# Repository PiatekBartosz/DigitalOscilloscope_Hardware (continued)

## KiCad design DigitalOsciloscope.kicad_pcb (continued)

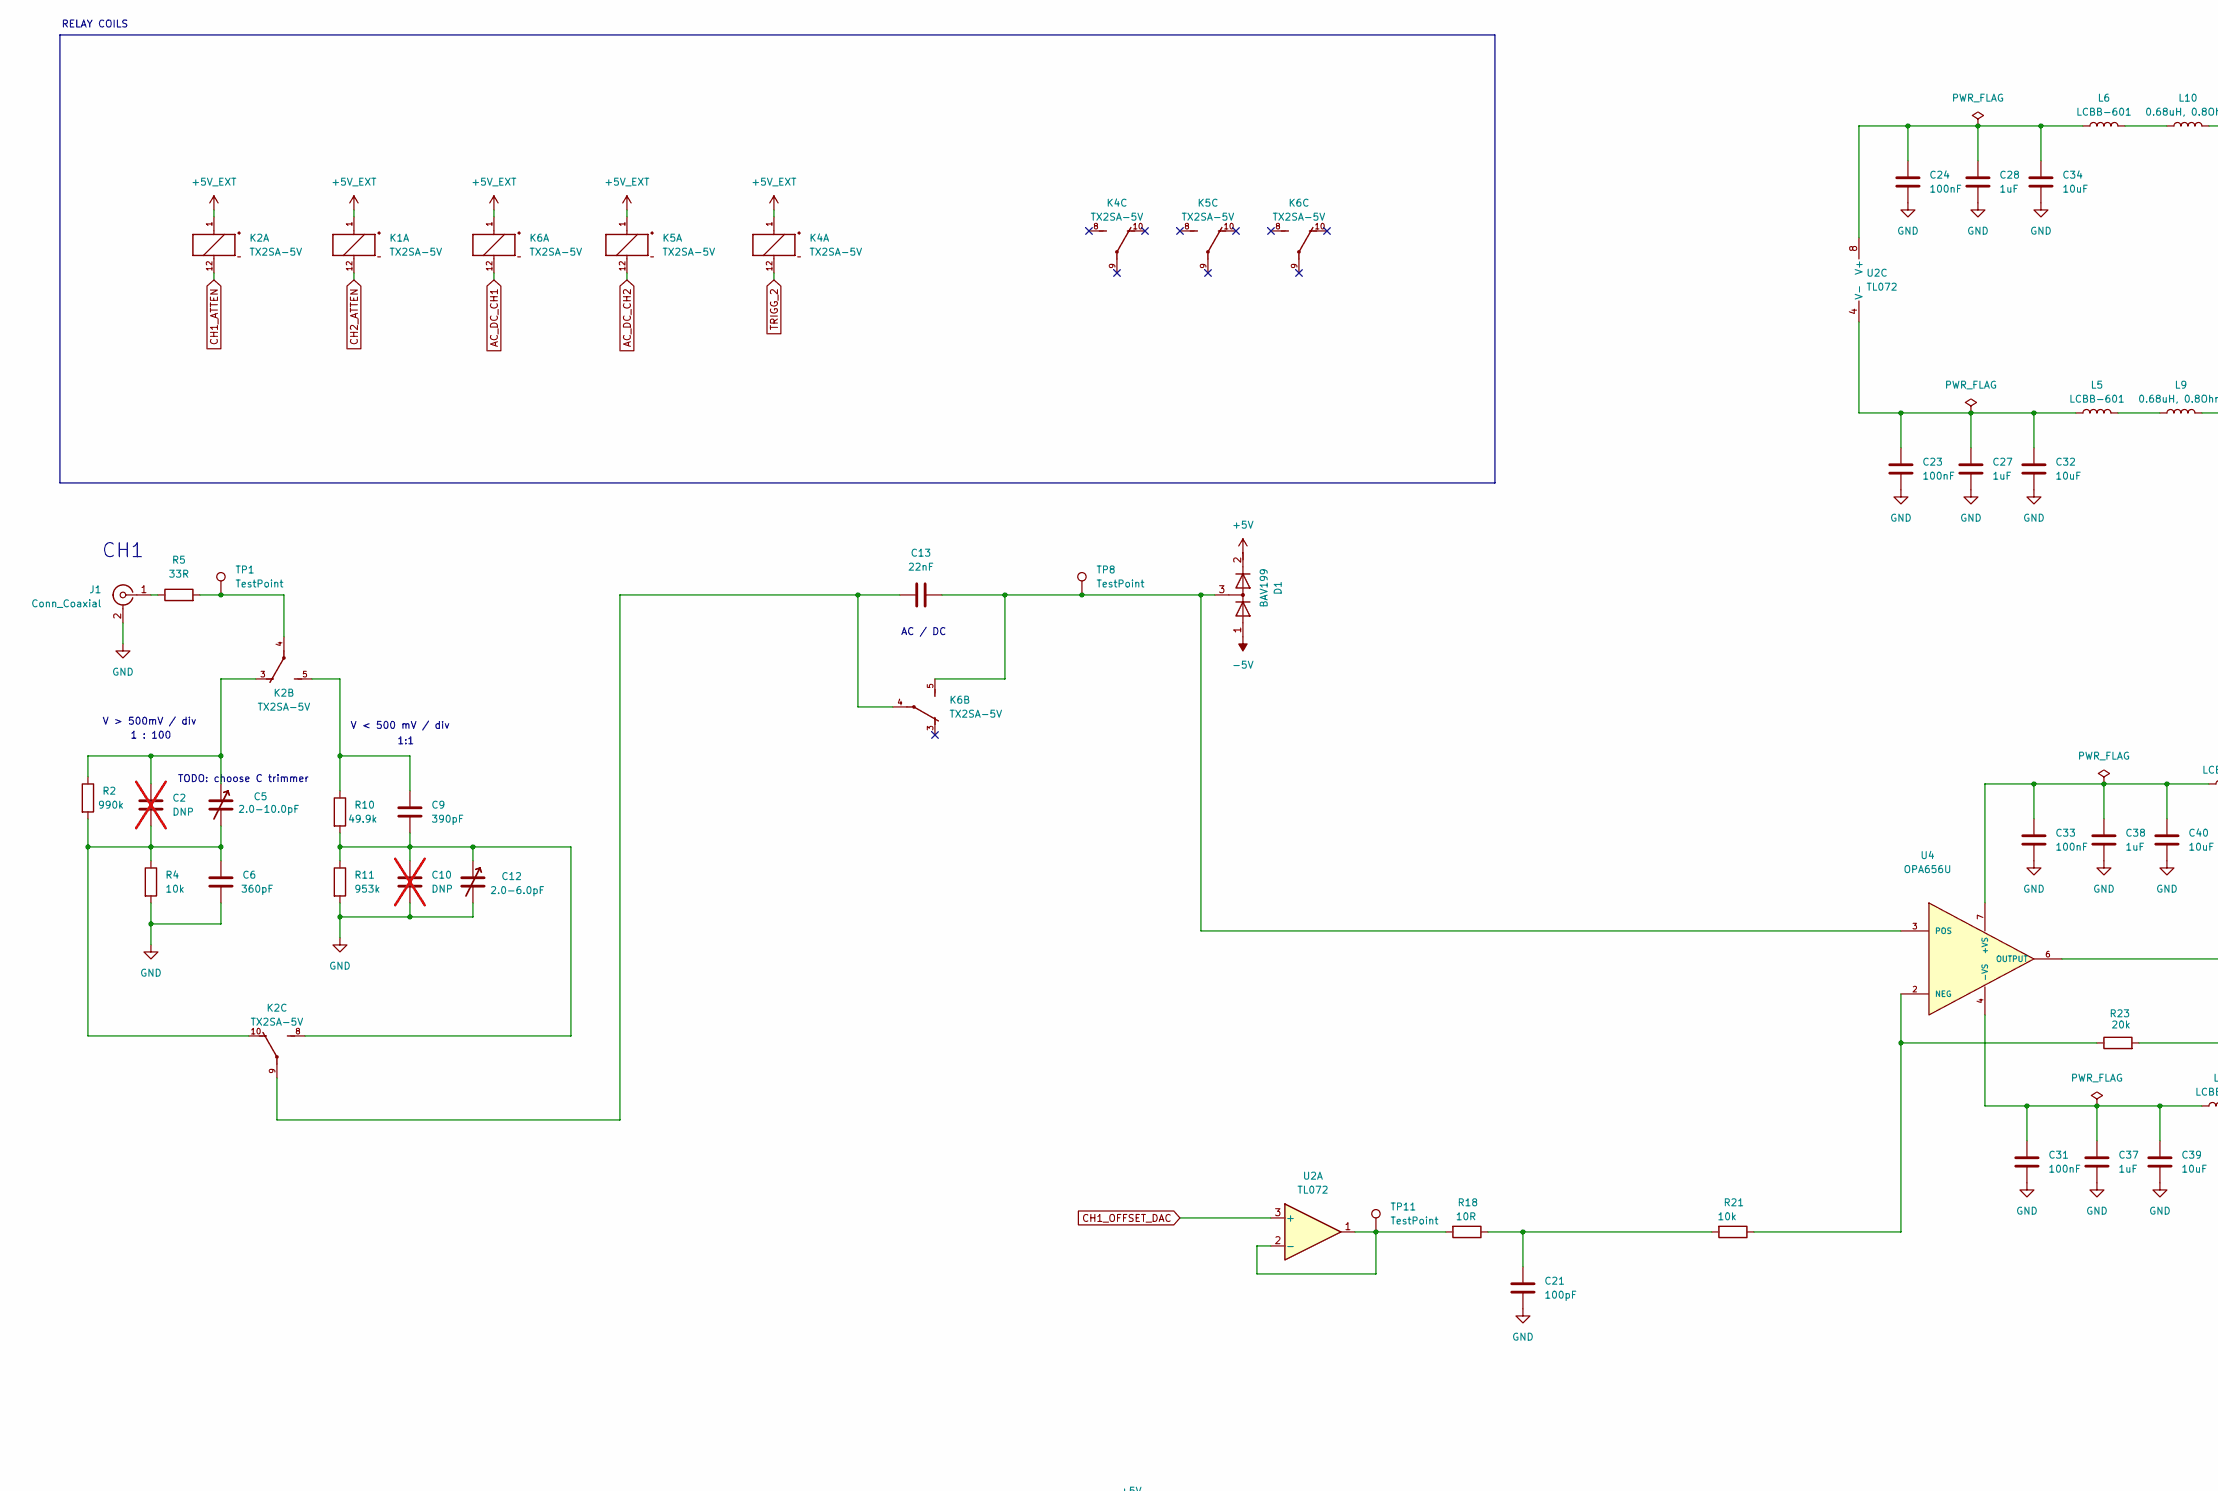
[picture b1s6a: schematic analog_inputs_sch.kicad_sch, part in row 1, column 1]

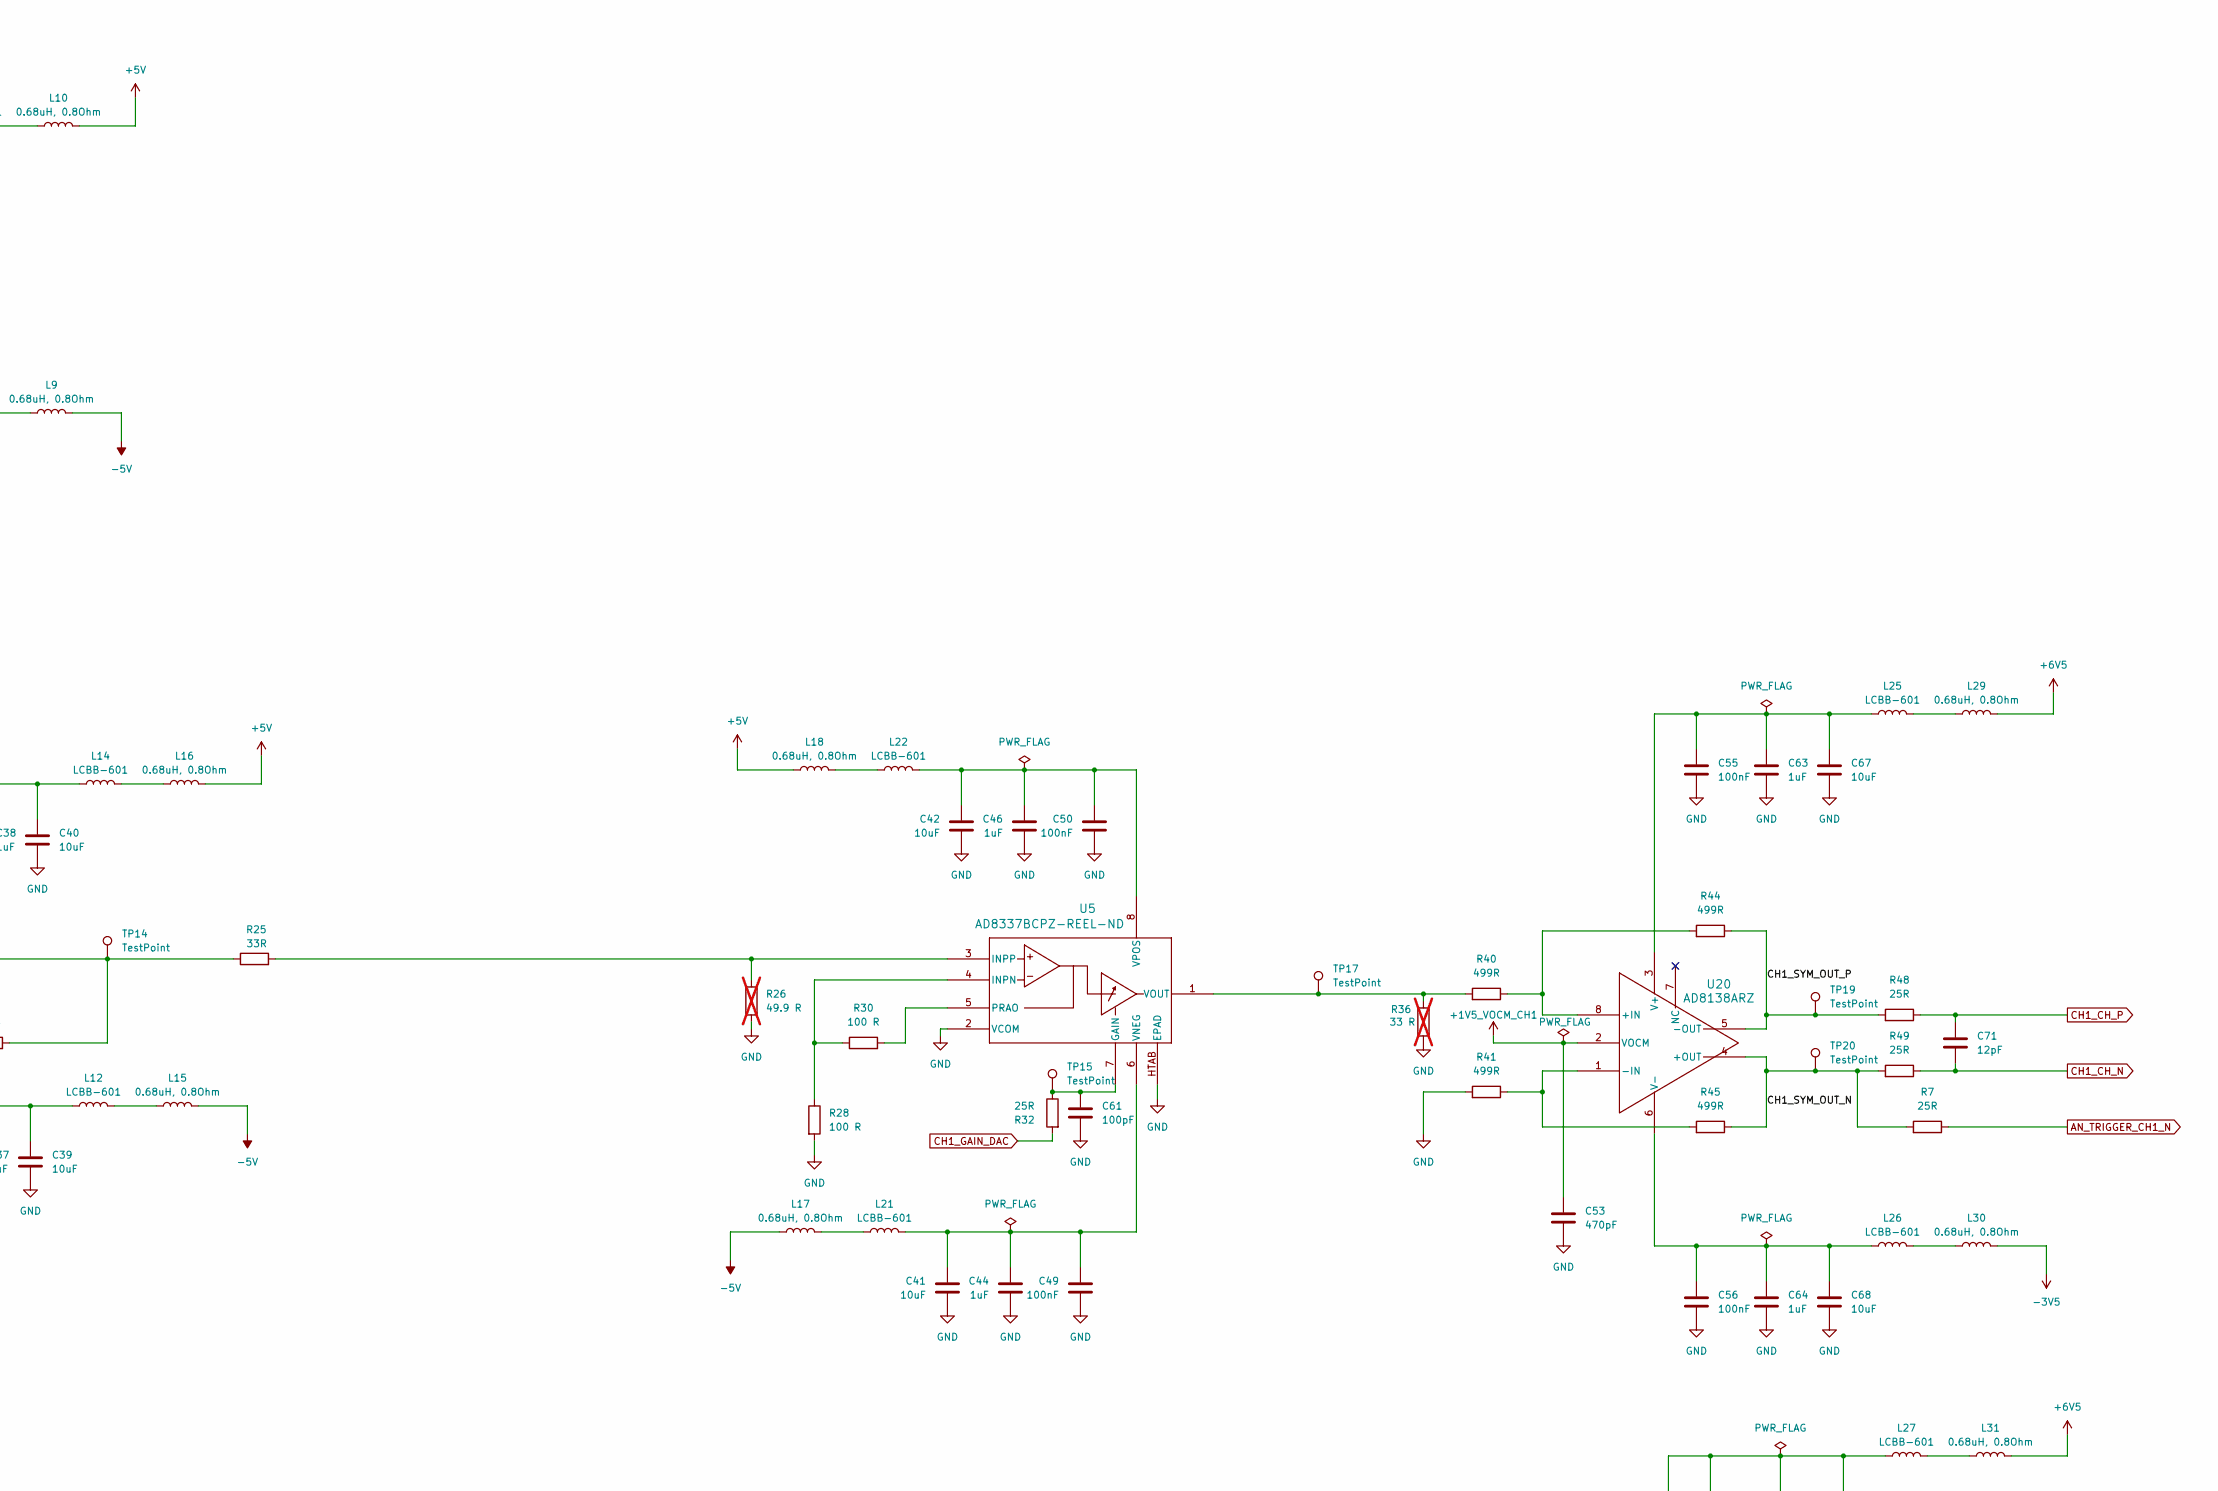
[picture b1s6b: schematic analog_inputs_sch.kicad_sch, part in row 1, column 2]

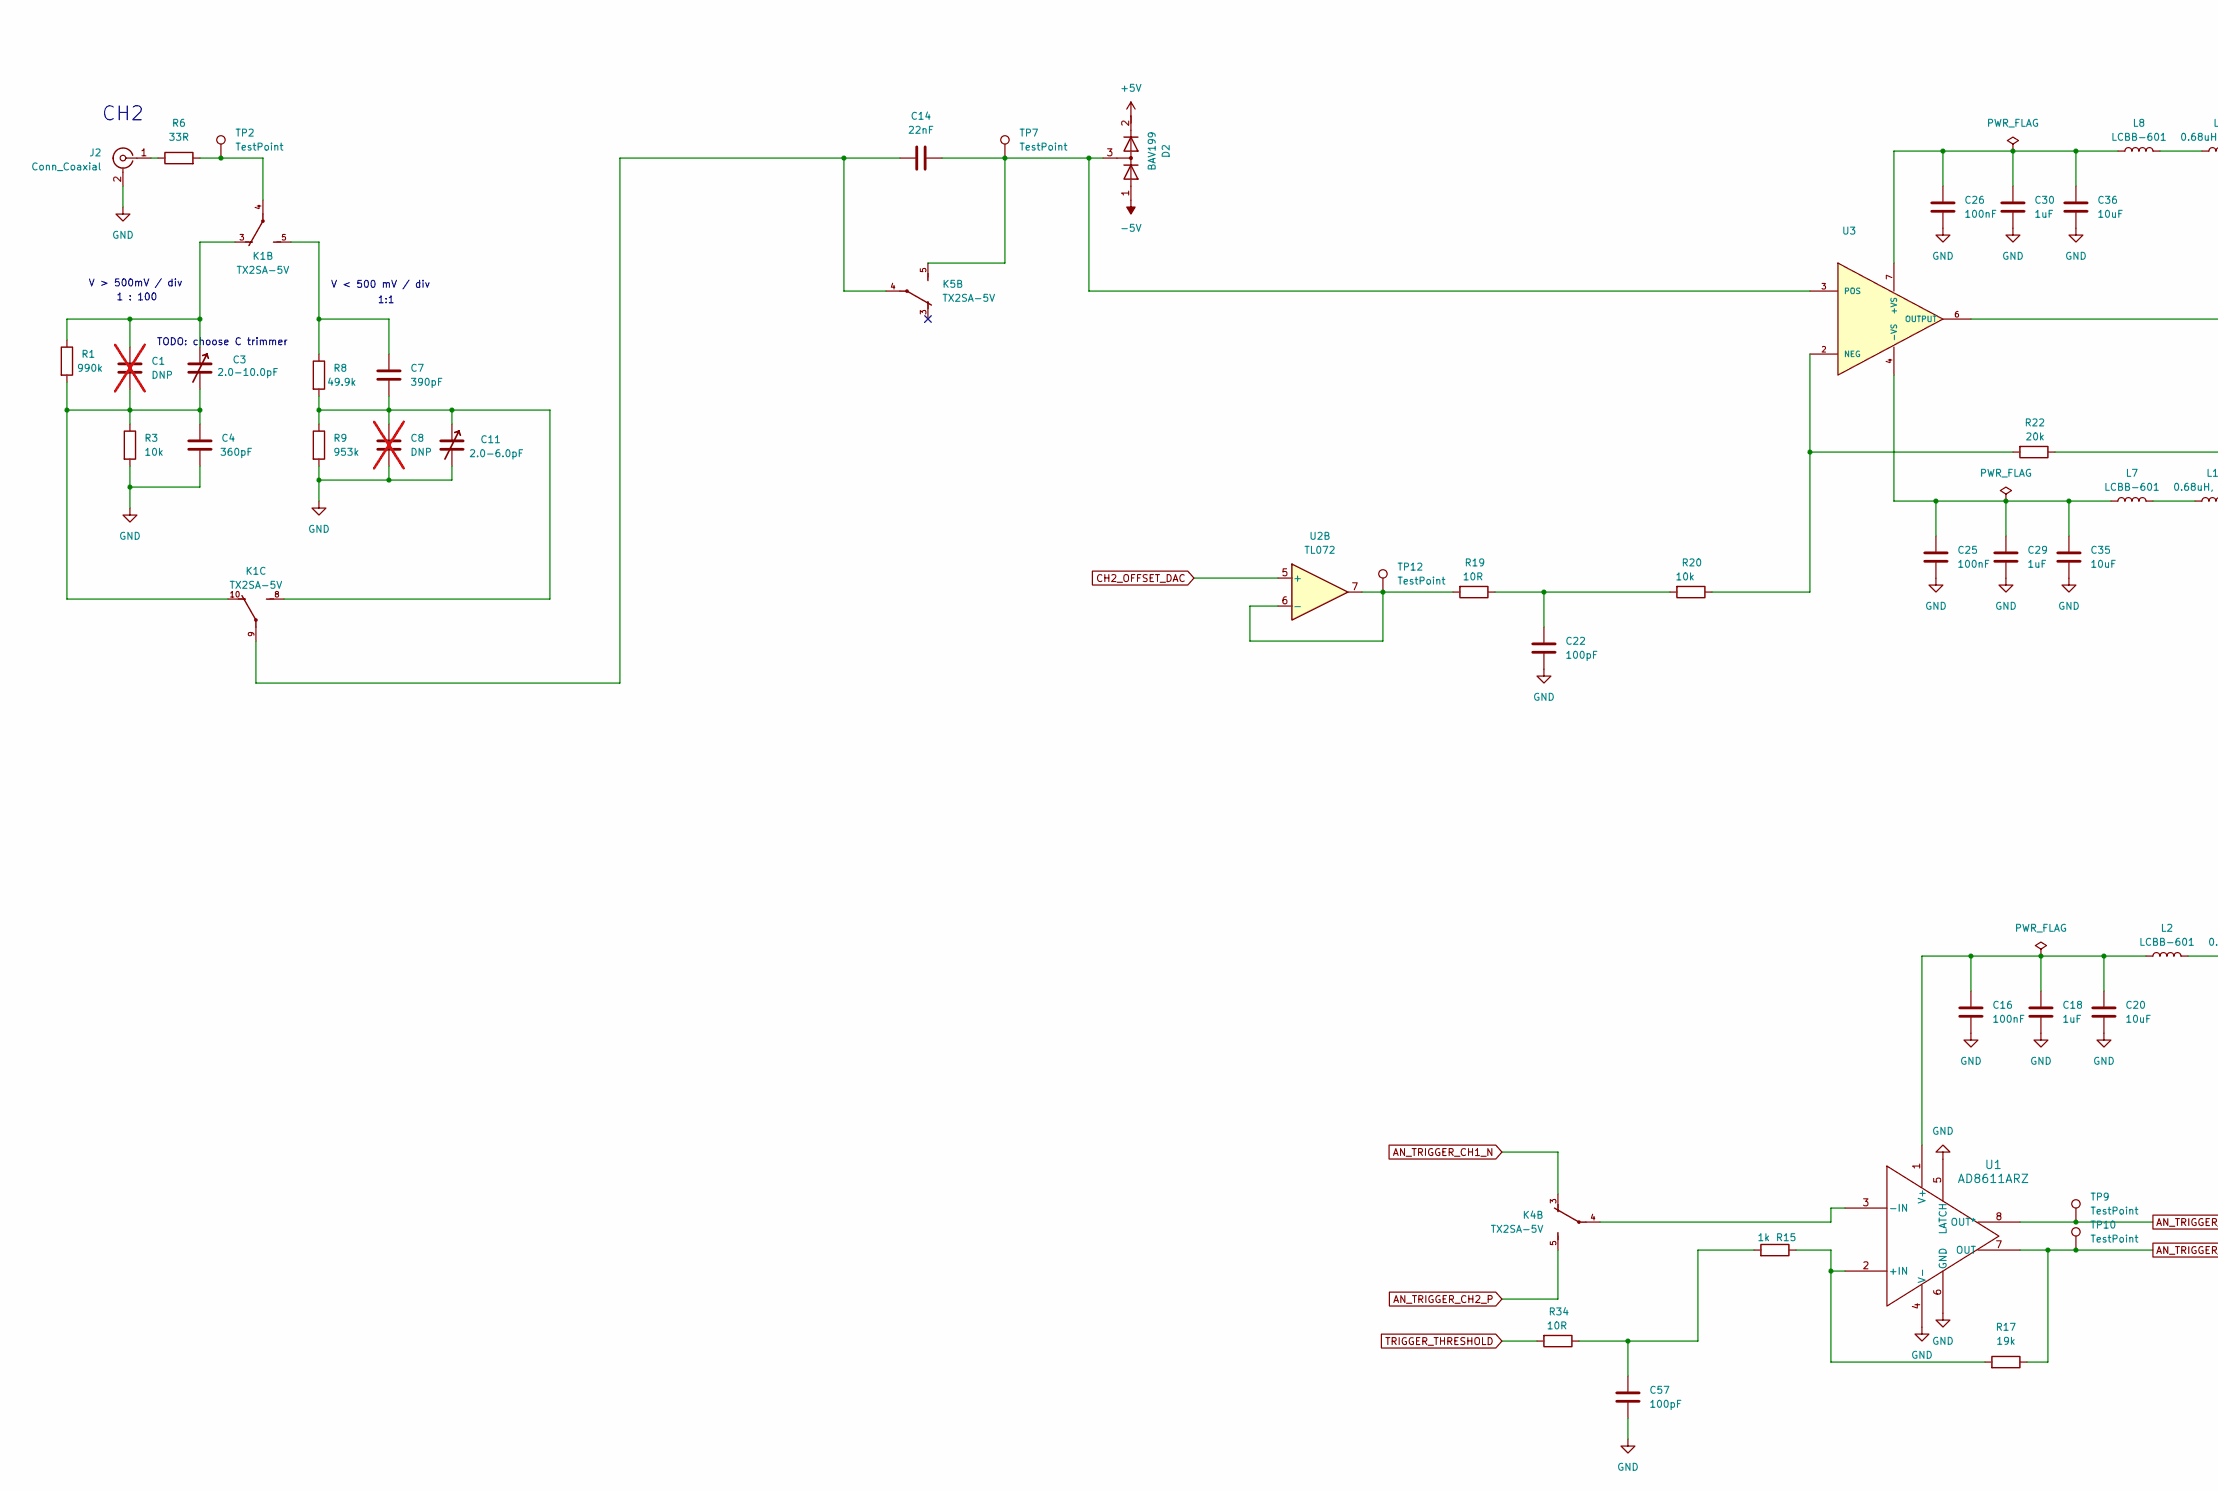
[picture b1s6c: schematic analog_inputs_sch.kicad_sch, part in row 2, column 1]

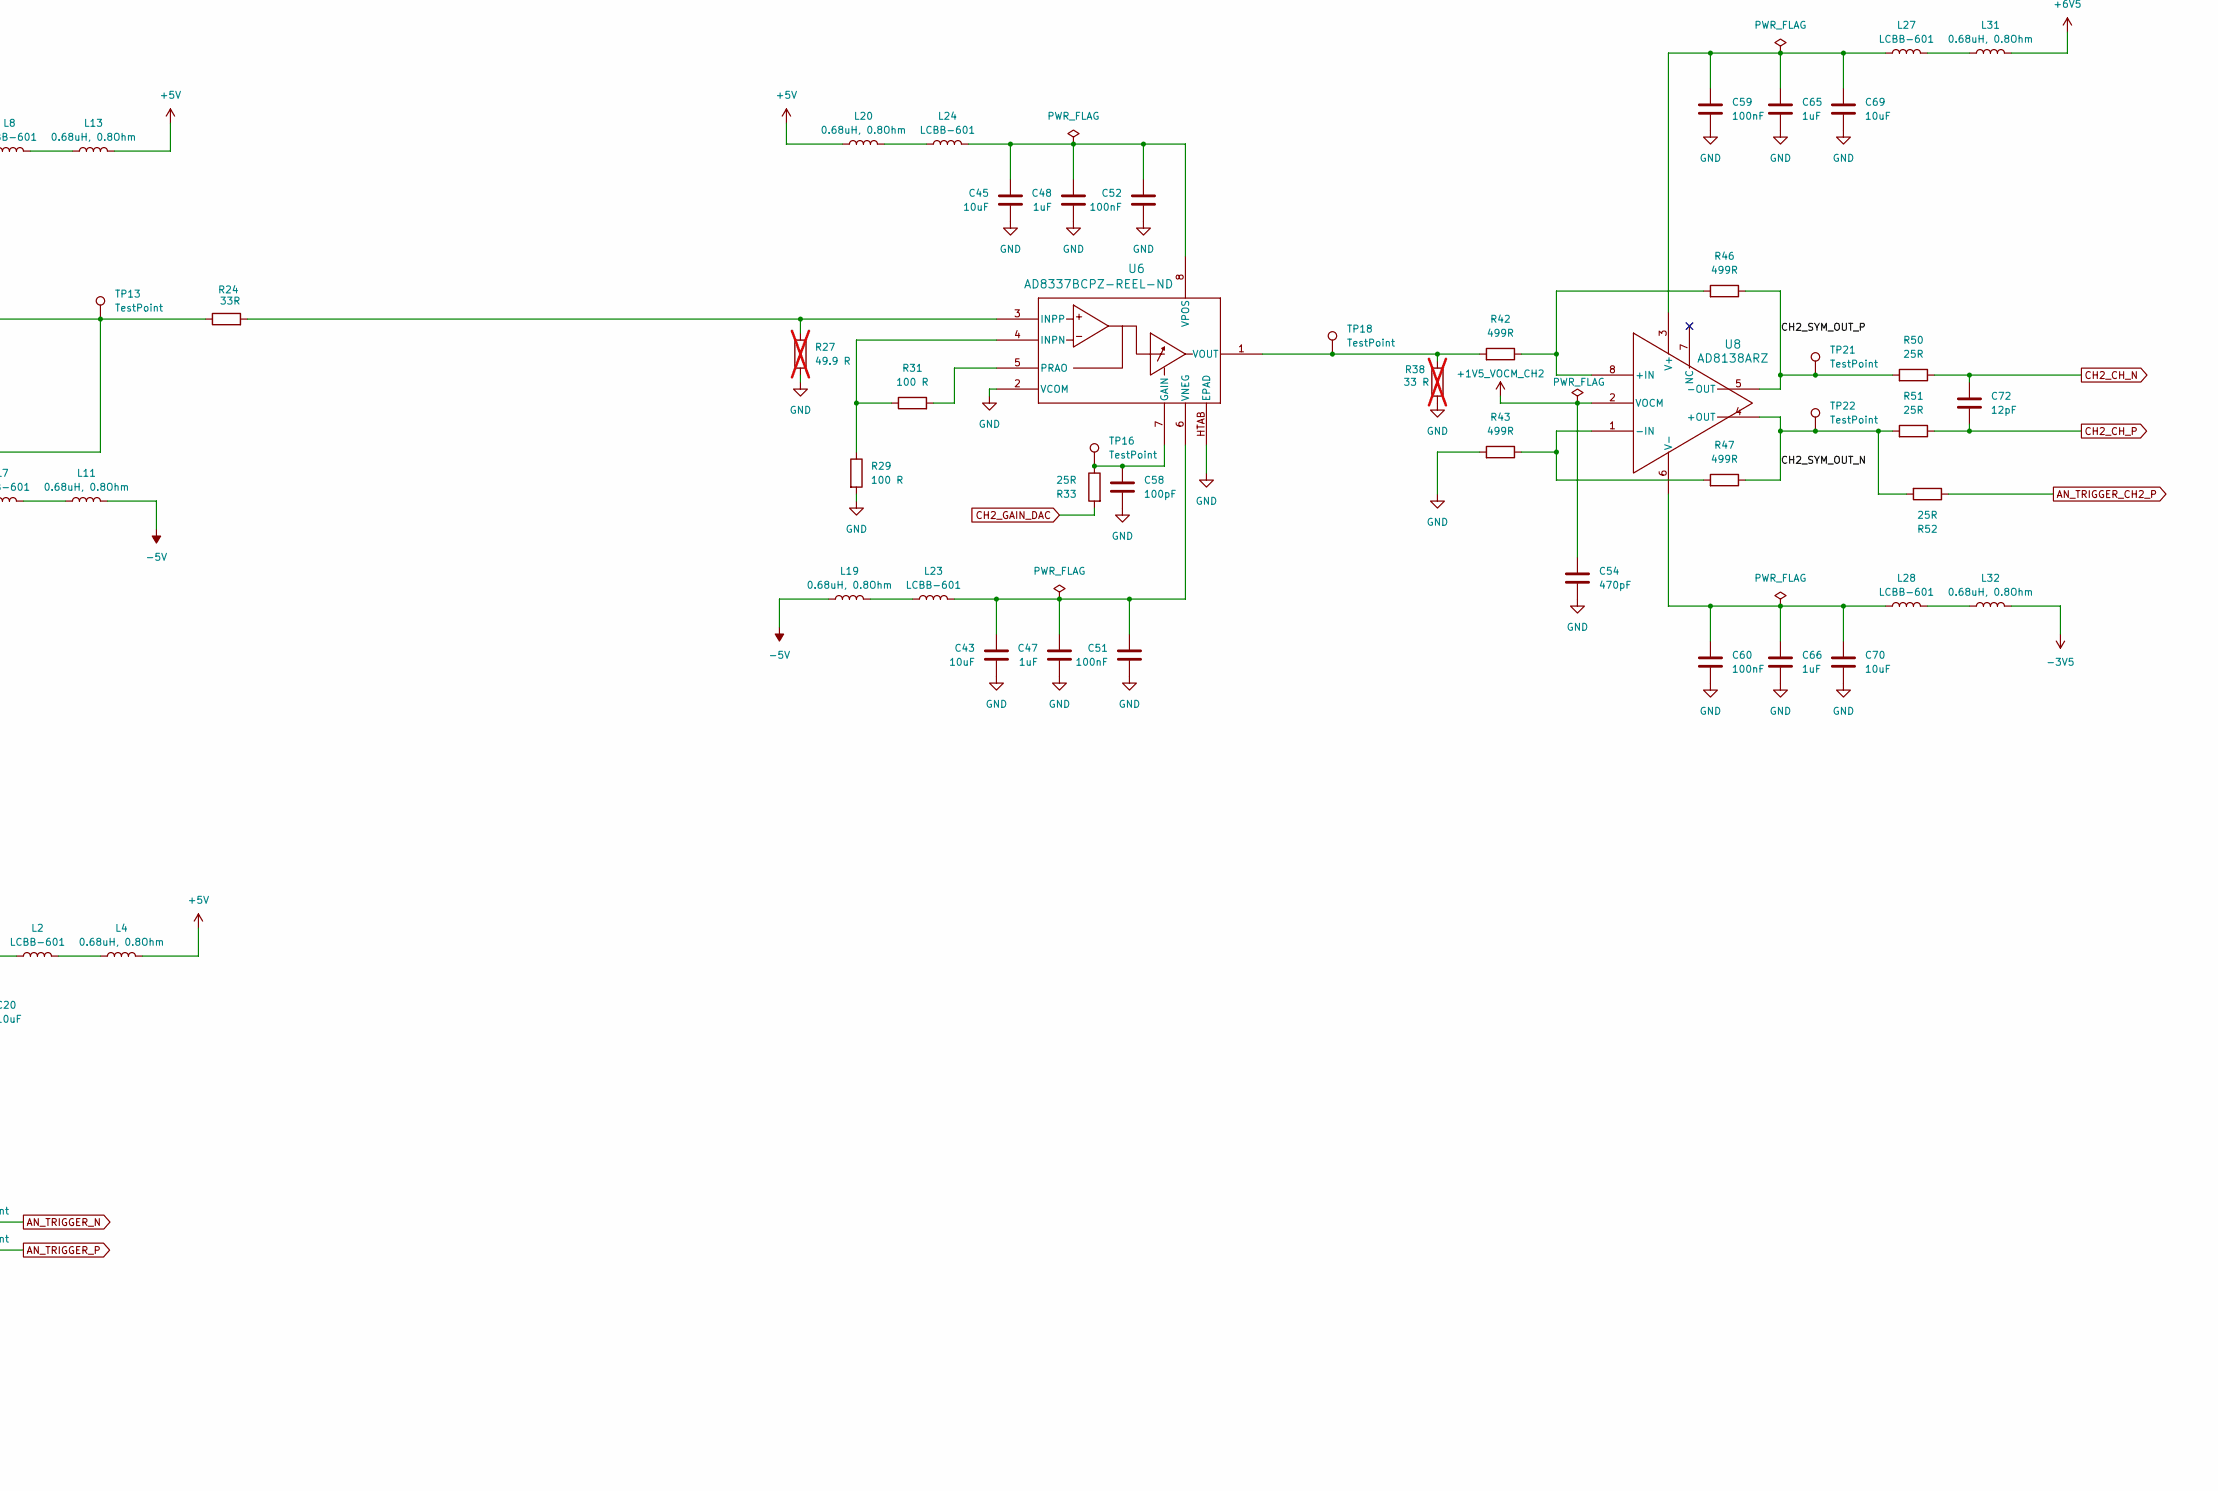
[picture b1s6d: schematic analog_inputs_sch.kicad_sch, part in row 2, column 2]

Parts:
C1, C2, C8, C10: DNP; C_0805_2012Metric; not fitted
C3, C5: 2.0-10.0pF; C_Trimmer_Voltronics_JZ
C4, C6: 360pF; C_0805_2012Metric
C7, C9: 390pF; C_0805_2012Metric
C11, C12: 2.0-6.0pF; C_Trimmer_Voltronics_JZ
C13, C14: 22nF; C_0805_2012Metric
C16, C23, C24, C25, C26, C31, C33, C49, C50, C51, C52, C55, C56, C59, C60: 100nF; C_0805_2012Metric
C18, C27, C28, C29, C30, C37, C38, C44, C46, C47, C48, C63, C64, C65, C66: 1uF; C_0805_2012Metric
C20, C32, C34, C35, C36, C39, C40, C41, C42, C43, C45, C67, C68, C69, C70: 10uF; C_0805_2012Metric
C21, C22, C57, C58, C61: 100pF; C_0805_2012Metric
C53, C54: 470pF; C_0805_2012Metric
C71, C72: 12pF; C_0805_2012Metric
D1, D2: BAV199; SOT-23
J1, J2: Conn_Coaxial; BNC_Amphenol_B6252HB-NPP3G-50_Horizontal
K1, K2, K4, K5, K6: TX2SA-5V; RELAY_TX2SA_PAN; FARNELL 1175716
L2, L5, L6, L7, L8, L12, L14, L21, L22, L23, L24, L25, L26, L27, L28: LCBB-601; L_0805_2012Metric
L4, L9, L10, L11, L13, L15, L16, L17, L18, L19, L20, L29, L30, L31, L32: 0.68uH, 0.8Ohm; L_0805_2012Metric
R1, R2: 990k; R_0805_2012Metric
R3, R4, R20, R21: 10k; R_0805_2012Metric
R5, R6, R24, R25: 33R; R_0805_2012Metric
R7, R32, R33, R48, R49, R50, R51, R52: 25R; R_0805_2012Metric
R8, R10: 49.9k; R_0805_2012Metric
R9, R11: 953k; R_0805_2012Metric
R15: 1k; R_0805_2012Metric
R17: 19k; R_0805_2012Metric
R18, R19, R34: 10R; R_0805_2012Metric
R22, R23: 20k; R_0805_2012Metric
R26, R27: 49.9 R; R_0805_2012Metric; not fitted
R28, R29, R30, R31: 100 R; R_0805_2012Metric
R36, R38: 33 R; R_0805_2012Metric; not fitted
R40, R41, R42, R43, R44, R45, R46, R47: 499R; R_0805_2012Metric
TP1, TP2, TP7, TP8, TP9, TP10, TP11, TP12, TP13, TP14, TP15, TP16, TP17, TP18, TP19, TP20, TP21, TP22: TestPoint; TestPoint_Pad_D1.0mm
U1: AD8611ARZ; R_8_ADI-L
U2: TL072; D8-L
U3, U4: OPA656U; SOIC127P599X175-8N
U5, U6: AD8337BCPZ-REEL-ND; CP_8_2_ADI-L
U8, U20: AD8138ARZ; R_8_ADI-L

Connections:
+1V5_VOCM_CH1: C53.1, U20.2 (VOCM); also elsewhere on the board
+1V5_VOCM_CH2: C54.1, U8.2 (VOCM); also elsewhere on the board
+5V: D1.2 (K2), D2.2 (K2), L4.1, L10.1, L13.1, L16.1, L18.1, L20.1; also elsewhere on the board
+5V_EXT: K1.1, K2.1, K4.1, K5.1, K6.1; also elsewhere on the board
+6V5: L29.1, L31.1; also elsewhere on the board
-3V5: L30.1, L32.1; also elsewhere on the board
-5V: D1.1 (A1), D2.1 (A1), L9.1, L11.1, L15.1, L17.1, L19.1; also elsewhere on the board
/analog_inputs/CH1_SYM_OUT_N: R7.2, R45.1, R49.2, TP20.1, U20.4 (+OUT)
/analog_inputs/CH1_SYM_OUT_P: R44.1, R48.2, TP19.1, U20.5 (-OUT)
/analog_inputs/CH2_SYM_OUT_N: R47.1, R51.2, R52.2, TP22.1, U8.4 (+OUT)
/analog_inputs/CH2_SYM_OUT_P: R46.1, R50.2, TP21.1, U8.5 (-OUT)
AC_DC_CH1: K6.12; also elsewhere on the board
AC_DC_CH2: K5.12; also elsewhere on the board
AN_TRIGGER_CH1_N: K4.3, R7.1
AN_TRIGGER_CH2_P: K4.5, R52.1
AN_TRIGGER_N: TP9.1, U1.8 (OUT*); also elsewhere on the board
AN_TRIGGER_P: R17.1, TP10.1, U1.7 (OUT); also elsewhere on the board
CH1_ATTEN: K2.12; also elsewhere on the board
CH1_CH_N: C71.2, R49.1; also elsewhere on the board
CH1_CH_P: C71.1, R48.1; also elsewhere on the board
CH1_GAIN_DAC: R32.2; also elsewhere on the board
CH1_OFFSET_DAC: U2.3 (+); also elsewhere on the board
CH2_ATTEN: K1.12; also elsewhere on the board
CH2_CH_N: C72.1, R50.1; also elsewhere on the board
CH2_CH_P: C72.2, R51.1; also elsewhere on the board
CH2_GAIN_DAC: R33.2; also elsewhere on the board
CH2_OFFSET_DAC: U2.5 (+); also elsewhere on the board
GND: C4.2, C6.2, C8.2, C10.2, C11.2, C12.2, C16.2, C18.1, C20.1, C21.1, C22.1, C23.2, C24.2, C25.2, C26.2, C27.1, C28.1, C29.1, C30.1, C31.2, C32.1, C33.2, C34.1, C35.1, C36.1, C37.1, C38.1, C39.1, C40.1, C41.1, C42.1, C43.1, C44.1, C45.1, C46.1, C47.1, C48.1, C49.2, C50.2, C51.2, C52.2, C53.2, C54.2, C55.2, C56.2, C57.1, C58.1, C59.2, C60.2, C61.1, C63.1, C64.1, C65.1, C66.1, C67.1, C68.1, C69.1, C70.1, J1.2 (Ext), J2.2 (Ext), R3.2, R4.2, R9.2, R11.2, R26.2, R27.2, R28.2, R29.2, R36.2, R38.2, R41.2, R43.2, U1.4 (V-), U1.5 (LATCH), U1.6 (GND), U5.2 (VCOM), U5.HTAB (EPAD), U6.2 (VCOM), U6.HTAB (EPAD); also elsewhere on the board
unnamed: C1.1, C3.1, K1.3, R1.1
unnamed: C1.2, C3.2, C4.1, K1.10, R1.2, R3.1
unnamed: C2.1, C5.1, K2.3, R2.1
unnamed: C2.2, C5.2, C6.1, K2.10, R2.2, R4.1
unnamed: C7.1, K1.5, R8.1
unnamed: C9.1, K2.5, R10.1
unnamed: C9.2, C10.1, C12.1, K2.8, R10.2, R11.1
unnamed: C7.2, C8.1, C11.1, K1.8, R8.2, R9.1
unnamed: C13.1, K2.9, K6.4
unnamed: C14.1, K1.9, K5.4
unnamed: C21.2, R18.1, R21.2
unnamed: C22.2, R19.1, R20.2
unnamed: C57.2, R15.2, R34.1
unnamed: C13.2, D1.3 (K3A4), K6.5, TP8.1, U4.3 (POS)
unnamed: C14.2, D2.3 (K3A4), K5.5, TP7.1, U3.3 (POS)
unnamed: J1.1 (In), R5.1
unnamed: J2.1 (In), R6.1
unnamed: K1.4, R6.2, TP2.1
unnamed: K2.4, R5.2, TP1.1
unnamed: L2.1, L4.2
unnamed: L5.1, L9.2
unnamed: L6.1, L10.2
unnamed: L7.1, L11.2
unnamed: L12.1, L15.2
unnamed: L8.1, L13.2
unnamed: L14.1, L16.2
unnamed: L17.2, L21.1
unnamed: L18.2, L22.1
unnamed: L19.2, L23.1
unnamed: L20.2, L24.1
unnamed: L25.1, L29.2
unnamed: L26.1, L30.2
unnamed: L27.1, L31.2
unnamed: L28.1, L32.2
unnamed: R15.1, R17.2, U1.2 (+IN)
unnamed: K4.4, U1.3 (-IN)
unnamed: C16.1, C18.2, C20.2, L2.2, U1.1 (V+)
unnamed: R18.2, TP11.1, U2.1, U2.2 (-)
unnamed: R19.2, TP12.1, U2.6 (-), U2.7
unnamed: C24.1, C28.2, C34.2, L6.2, U2.8 (V+)
unnamed: C23.1, C27.2, C32.2, L5.2, U2.4 (V-)
unnamed: C26.1, C30.2, C36.2, L8.2, U3.7 (+VS)
unnamed: C25.1, C29.2, C35.2, L7.2, U3.4 (-VS)
unnamed: R20.1, R22.2, U3.2 (NEG)
unnamed: R22.1, R24.1, TP13.1, U3.6 (OUTPUT)
unnamed: C33.1, C38.2, C40.2, L14.2, U4.7 (+VS)
unnamed: C31.1, C37.2, C39.2, L12.2, U4.4 (-VS)
unnamed: R21.1, R23.1, U4.2 (NEG)
unnamed: R23.2, R25.1, TP14.1, U4.6 (OUTPUT)
unnamed: C61.2, R32.1, TP15.1, U5.7 (GAIN)
unnamed: R28.1, R30.1, U5.4 (INPN)
unnamed: R25.2, R26.1, U5.3 (INPP)
unnamed: R30.2, U5.5 (PRAO)
unnamed: C41.2, C44.2, C49.1, L21.2, U5.6 (VNEG)
unnamed: R36.1, R40.2, TP17.1, U5.1 (VOUT)
unnamed: C42.2, C46.2, C50.1, L22.2, U5.8 (VPOS)
unnamed: C58.2, R33.1, TP16.1, U6.7 (GAIN)
unnamed: R29.1, R31.1, U6.4 (INPN)
unnamed: R24.2, R27.1, U6.3 (INPP)
unnamed: R31.2, U6.5 (PRAO)
unnamed: C43.2, C47.2, C51.1, L23.2, U6.6 (VNEG)
unnamed: R38.1, R42.2, TP18.1, U6.1 (VOUT)
unnamed: C45.2, C48.2, C52.1, L24.2, U6.8 (VPOS)
unnamed: R42.1, R46.2, U8.8 (+IN)
unnamed: R43.1, R47.2, U8.1 (-IN)
unnamed: C59.1, C65.2, C69.2, L27.2, U8.3 (V+)
unnamed: C60.1, C66.2, C70.2, L28.2, U8.6 (V-)
unnamed: R40.1, R44.2, U20.8 (+IN)
unnamed: R41.1, R45.2, U20.1 (-IN)
unnamed: C55.1, C63.2, C67.2, L25.2, U20.3 (V+)
unnamed: C56.1, C64.2, C68.2, L26.2, U20.6 (V-)
TRIGGER_THRESHOLD: R34.2; also elsewhere on the board
TRIGG_2: K4.12; also elsewhere on the board

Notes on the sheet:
TODO: choose C trimmer
1 : 100
V < 500 mV / div
RELAY COILS
V > 500mV / div
1:1
CH1
CH2
AC / DC

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
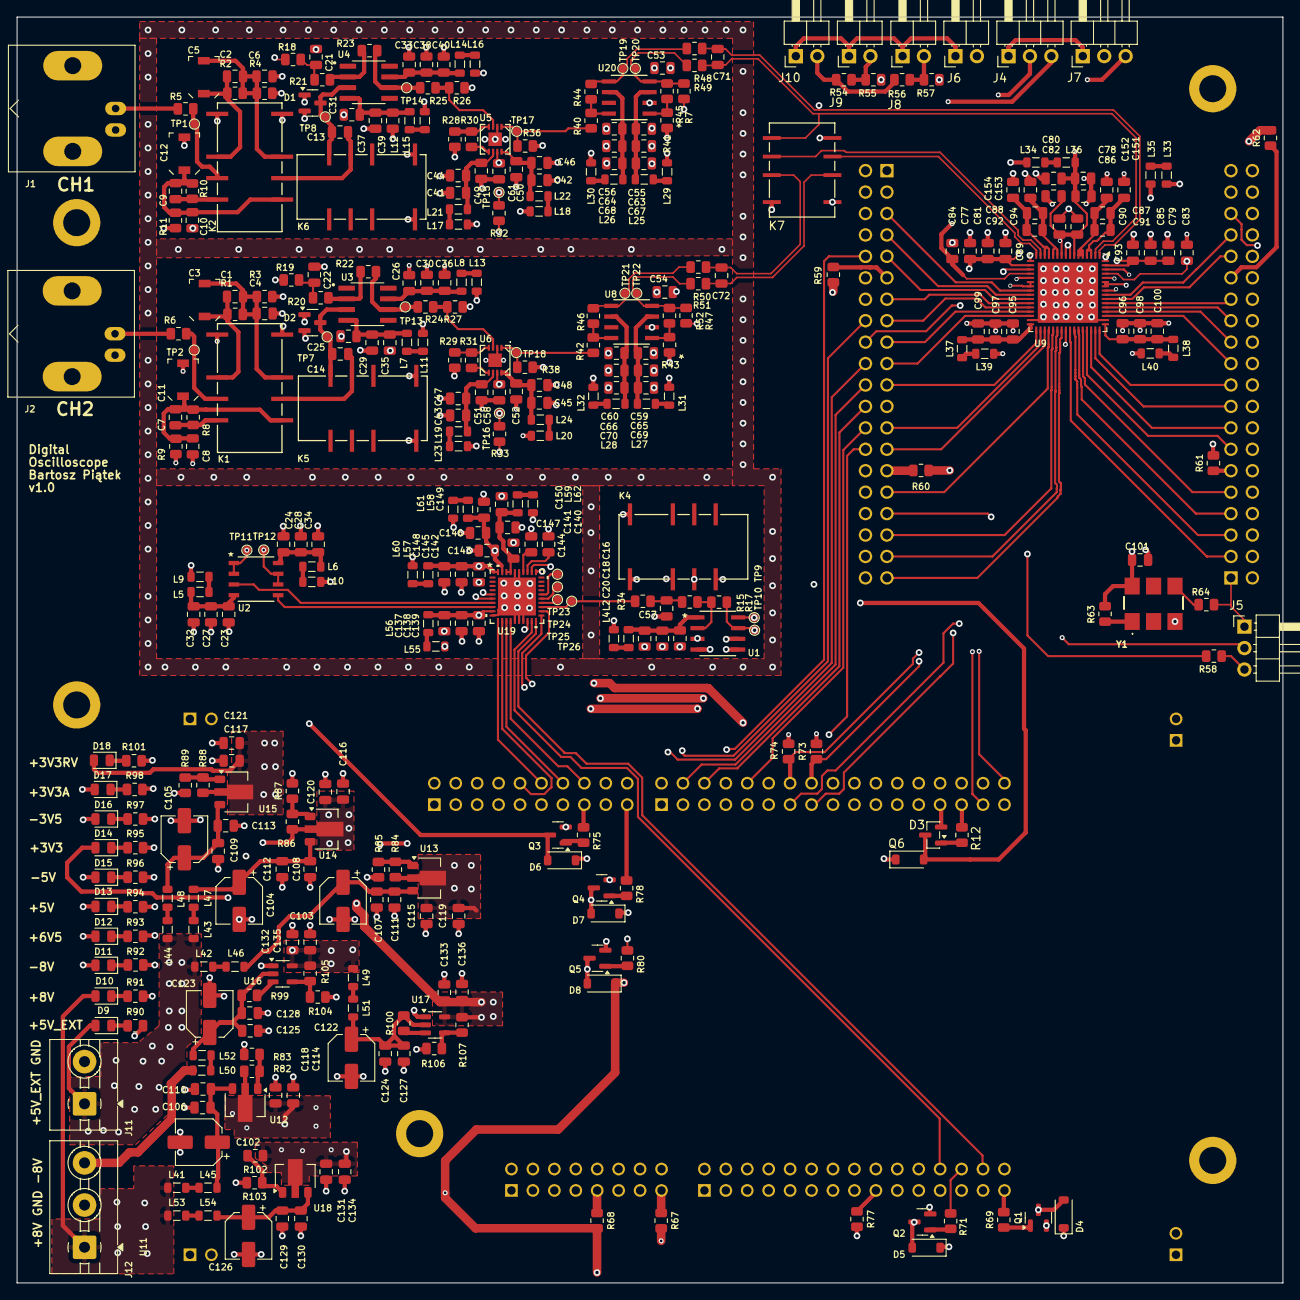
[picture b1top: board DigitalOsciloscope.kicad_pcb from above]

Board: 4 copper layers, 150.0 x 150.0 mm, 382 parts (1 on the bottom side), 266 nets.

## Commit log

2025-07-02 Initial work on analog frontend
2025-07-02 Save work
2025-07-13 First schematic version of AF
2025-07-14 Chose amplifiers
2025-07-15 Add some of the AF power supply levels
2025-07-31 Move the trigger
2025-08-06 First version of analog path, without resistor values
2025-08-08 Touch up analog front end, add base of the psu
2025-08-08 PCB edge, initial work on assigning footprints
2025-08-14 Link up ADC to FPGA
2025-08-18 Add connection between MCU and FPGA
2025-08-19 Add things to MCU on the board
2025-08-31 Save work on simplifying the desing
2025-08-31 Simplifying the design
2025-09-09 Save work on fixing analog front end
2025-09-10 Gain on diff amp 0.2
2025-09-15 Mostly finished schematics, without decoupling and power
2025-09-16 Finished schematic?
2025-10-09 Save work after calculating AF
2025-10-26 Almost finishing schematic
2025-10-26 Save work before deleting amps from DAC to offset
2025-10-27 Save work, I don't think we throw out the 2x amps
2025-10-27 Added first dirty BOM
2025-10-27 Add import BOM into excel
2025-10-27 Remove the stage between DAC and FET buffer
2025-10-28 Change PSU minus volltage regulators
2025-11-05 Finished up schematic? - Added missing PSU lines
2025-11-06 Start working on ERC, properly annotate DNP elements
2025-11-06 Fix ERC
2025-11-06 Add all footprints
2025-11-20 Apply changes after review, left to fix: comparator histeresis, PSU missing lines?
2025-11-21 Fix footprints and allign components placements
2025-11-22 Route AFE - attenuators
2025-11-22 Route up to symetric amplifier in CH1
2025-11-22 Save work before changing the pin header of FPGA connected to LTC2299
2025-11-22 Fix fpga ADC pin assignment
2025-11-22 Save before tuning the ADC FPGA networks:
2025-11-22 Save work before trying to add differential traces
2025-11-22 Save work before adding symetrical op amp
2025-11-23 Add LDO's
2025-11-23 Do most of the PCB
2025-11-23 Place all componenets
2025-11-23 Save before second attempt of routing ADC to FPGA
2025-11-23 Done routing FGPA ADC data lines
2025-11-23 Finish 5V_EXT?
2025-11-23 Route +5V and -5V
2025-11-23 Save work before routing FPGA to STM32
2025-11-23 Save work before trying to allign FPGA MCU traces
2025-11-23 Everything is routed
2025-11-23 Fix all DRC errors
2025-11-23 Generate first gerber files
2025-11-23 First version of gerber files
2025-11-23 Place most of the components in cart
2025-11-29 Save work before reworking relay symbol
2025-11-30 Remove old relays, assign footprints to SMD relays
2025-11-30 Finish channel 1 rework
2025-11-30 Place all elements after rework
2025-12-01 Finish release condidate 2
2025-12-01 Fix bug in adc ref voltage
2025-12-01 Fixup shield, move BNC connectors out of the AFE shield enclosure
2025-12-07 Trying to add symetry
2025-12-13 Pcb review changes
2025-12-14 Changes after major PCB review
2025-12-14 PCB review routing rework, before globally deleting hanging tracks and vias
2025-12-14 PCB review changes implemented
2025-12-14 Generate new gerber files after PCB review
2025-12-16 Interleaved channel 1 / channel 2
2025-12-16 Allign and distribute vias
2025-12-16 Add zipped gerbers after via rework
2025-12-16 Gerber review changes, add mounting holes
